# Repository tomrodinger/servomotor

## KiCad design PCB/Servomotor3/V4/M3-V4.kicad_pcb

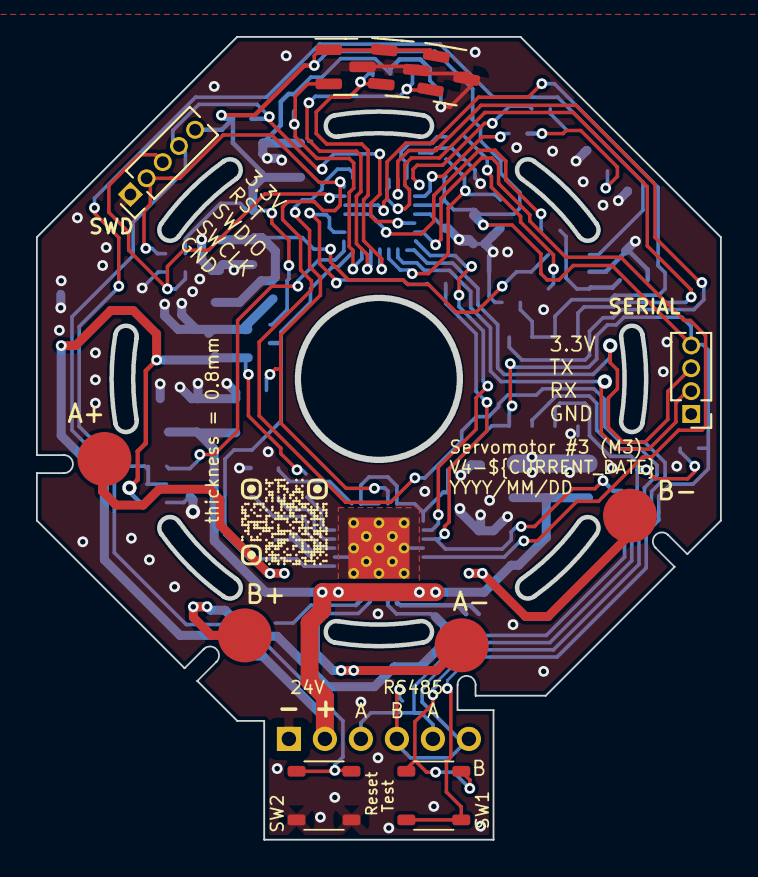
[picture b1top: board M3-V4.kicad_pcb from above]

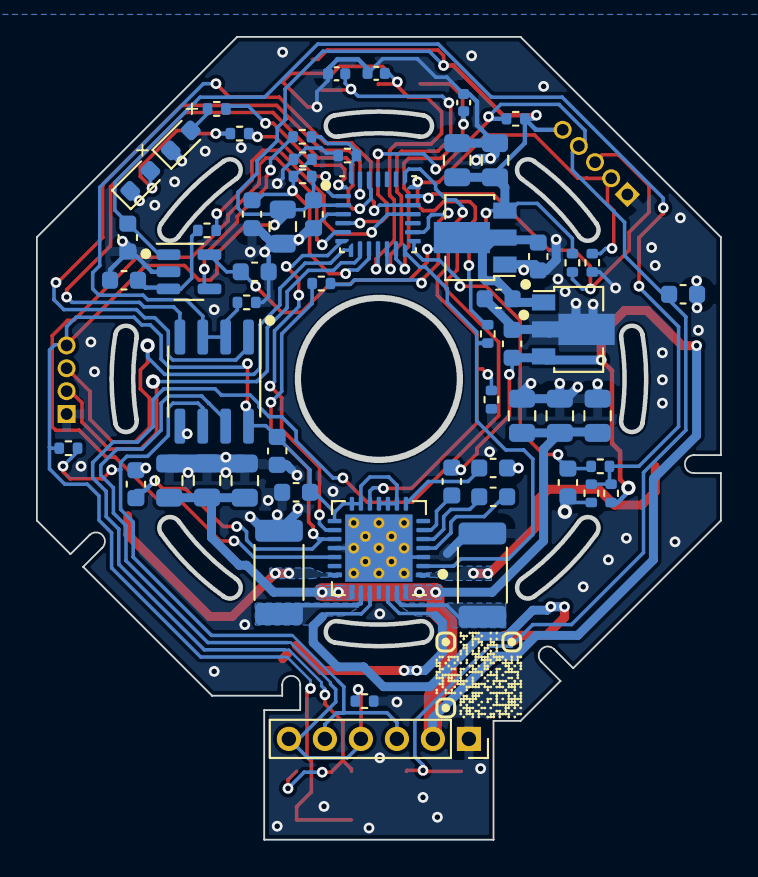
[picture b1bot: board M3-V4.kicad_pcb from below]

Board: 2 copper layers, 38.0 x 44.6 mm, 69 parts (58 on the bottom side), 44 nets.

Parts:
C1, C2, C3, C18, C25, C28, C35, C36, C37: 100nF; C_0603_1608Metric
C4, C6: 220nF; C_0603_1608Metric
C5, C7, C8, C9, C12, C14, C15, C19, C33: 4.7uF; C_0805_2012Metric
C17, C20, C23: 1nF; C_0402_1005Metric
C22, C26, C32, C41: 1uF; C_0603_1608Metric
C30: 100pF; C_0603_1608Metric
D3: KT-0603R; LED_0603_1608Metric
D4: 19-217/GHC-YR1S2/3T; LED_0603_1608Metric
J1: 01x04 male P=1.27mm; PinHeader_1x04_P1.27mm_Vertical
J2: 01x05 male P=1.27mm; PinHeader_1x05_P1.27mm_Vertical
J3, J6, J7, J8: Conn_01x01_Socket; Pad_3mm_TopOnly
J4: Conn_01x06_Socket; PinSocket_1x06_P2.00mm_Vertical
R1, R3: 270m; R_2010_5025Metric
R2, R4, R5, R7, R13, R15, R17, R20, R22, R24, R25, R27: 10k; R_0402_1005Metric
R6, R23: 5.6k; R_0402_1005Metric
R11: 470R; R_0402_1005Metric
R12: 1.5k; R_0402_1005Metric
R26: 1K; R_0402_1005Metric
R29: 4.7k; R_0402_1005Metric
SW1, SW2: TS3735PA-250gf
TH1: 100k 1% NTC; R_0402_1005Metric
U4, U6, U7: AH49HSC; SOT-23
U5: A4988; QFN-28-1EP_5x5mm_P0.5mm_EP3.75x3.75mm_ThermalVias_0.3mm
U8: STM32G031G8U6; QFN-28_4x4mm_P0.5mm
U9: LM321; SOT-23-5
U10: SP3485EN; SOIC-8_3.9x4.9mm_P1.27mm
U11: HT7533-1; SOT-89-3
U12: L78L10_SOT89; SOT-89-3

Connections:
+3.3V: C5.1, C6.1, C9.1, C33.1, C35.2, C37.1, J1.4, J2.5, R5.2, R6.2, R15.2, R17.2, R29.2, SW1.1, U4.1 (VCC), U5.9 (MS1), U5.10 (MS2), U5.11 (MS3), U5.13 (ROSC), U5.14 (~SLEEP), U5.15 (VDD), U6.1 (VCC), U7.1 (VCC), U8.3 (VDD), U10.8 (VCC), U11.3 (VOUT)
+10V: C22.1, C26.1, C32.1, U9.5 (V+), U11.2 (VIN), U12.1 (OUT)
+24V: C3.1, C7.1, C8.1, C12.1, C14.1, C15.1, C19.1, C25.1, J4.2, R27.1, U5.22 (VBB1), U5.28 (VBB2), U12.3 (IN)
/index/schTop/A: J4.3, J4.5, R17.1, U10.6 (A)
/index/schTop/B: J4.4, J4.6, R2.2, U10.7 (B)
/index/schTop/DIR: U5.19 (DIR), U8.6 (PA0)
/index/schTop/HALL1: C17.1, U7.2 (VOUT), U8.11 (PA5)
/index/schTop/HALL2: C20.1, U6.2 (VOUT), U8.12 (PA6)
/index/schTop/HALL3: C23.1, U4.2 (VOUT), U8.13 (PA7)
/index/schTop/IMCONTROL: R22.1, U8.16 (PA8)
/index/schTop/LED_GREEN: R11.1, U8.2 (PC15)
/index/schTop/LED_RED: R12.1, U8.1 (PC14)
/index/schTop/OUT1A: J7.1, U5.24 (OUT1A)
/index/schTop/OUT1B: J6.1, U5.21 (OUT1B)
/index/schTop/OUT2A: J3.1, U5.26 (OUT2A)
/index/schTop/OUT2B: J8.1, U5.1 (OUT2B)
/index/schTop/OVER_VOLTAGE: R20.2, R23.2, U8.28 (PB8)
/index/schTop/PWMOV: R25.1, U8.18 (PA11/PA9)
/index/schTop/REF24: C36.1, R24.1, U8.15 (PB1)
/index/schTop/RESET: C18.1, J2.4, R15.1, SW2.1, U8.5 (PF2)
/index/schTop/RS485_D: U8.26 (PB6), U10.4 (DI)
/index/schTop/RS485_EN: R13.2, U8.19 (PA12/PA10), U10.2 (~RE), U10.3 (DE)
/index/schTop/RS485_R: U8.27 (PB7), U10.1 (RO)
/index/schTop/STEP: U5.16 (STEP), U8.7 (PA1)
/index/schTop/SWCLK: J2.2, R4.2, SW1.2, U8.21 (PA14)
/index/schTop/SWDIO: J2.3, R5.1, U8.20 (PA13)
/index/schTop/TEMPERATURE: C41.1, R29.1, TH1.1, U8.10 (PA4)
/index/schTop/UART2 RX: J1.2, U8.9 (PA3)
/index/schTop/UART2 TX: J1.3, U8.8 (PA2)
/index/schTop/VREF: C1.1, R22.2, U5.17 (VREF)
/index/schTop/~MENABLE: R6.1, U5.2 (~ENABLE), U8.14 (PB0)
/index/schTop/~MRESET: R7.2, U5.12 (~RESET), U8.22 (PA15)
GND: C1.2, C4.1, C5.2, C6.2, C7.2, C8.2, C9.2, C12.2, C14.2, C15.2, C17.2, C18.2, C19.2, C20.2, C22.2, C23.2, C25.2, C26.2, C28.2, C30.2, C32.2, C33.2, C35.1, C36.2, C37.2, C41.2, D3.1 (K), D4.1 (K), J1.1, J2.1, J4.1, R1.1, R2.1, R3.1, R4.1, R7.1, R13.1, R23.1, R26.2, SW2.2, TH1.2, U4.3 (GND), U5.3 (GND), U5.18 (GND), U5.29 (PAD), U6.3 (GND), U7.3 (GND), U8.4 (VSS), U9.2 (V-), U10.5 (GND), U11.1 (GND), U12.2 (GND)
unnamed: D3.2 (A), R12.2
unnamed: D4.2 (A), R11.2
unnamed: R20.1, U9.4
unnamed: C2.1, U5.4 (CP1)
unnamed: C2.2, U5.5 (CP2)
unnamed: R1.2, U5.23 (SENSE1)
unnamed: R3.2, U5.27 (SENSE2)
unnamed: C3.2, U5.6 (VCP)
unnamed: C4.2, U5.8 (VREG)
unnamed: C30.1, R24.2, R26.1, R27.2, U9.1 (+)
unnamed: C28.1, R25.2, U9.3 (-)

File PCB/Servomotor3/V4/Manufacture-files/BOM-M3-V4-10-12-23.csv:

Designator,Comment,Footprint,LCSC
"C1, C2, C3, C18, C25, C28, C35, C36, C37",100nF,Capacitor_SMD:C_0603_1608Metric,C14663
"C4, C6",220nF,Capacitor_SMD:C_0603_1608Metric,C21120
"C5, C7, C8, C9, C12, C14, C15, C19, C33",4.7uF,Capacitor_SMD:C_0805_2012Metric,C1779
"C17, C20, C23",1nF,Capacitor_SMD:C_0402_1005Metric,C1523
"C22, C26, C32, C41",1uF,Capacitor_SMD:C_0603_1608Metric,C15849
C30,100pF,Capacitor_SMD:C_0603_1608Metric,C14858
D3,KT-0603R,LED_SMD:LED_0603_1608Metric,C2286
D4,19-217/GHC-YR1S2/3T,LED_SMD:LED_0603_1608Metric,C72043
"R1, R3",270m,Resistor_SMD:R_2010_5025Metric,C303758
"R2, R4, R5, R7, R13, R15, R17, R20, R22, R24, R25, R27",10k,Resistor_SMD:R_0402_1005Metric,C25744
"R6, R23",5.6k,Resistor_SMD:R_0402_1005Metric,C25908
R11,470R,Resistor_SMD:R_0402_1005Metric,C25117
R12,1.5k,Resistor_SMD:R_0402_1005Metric,C25867
R26,1K,Resistor_SMD:R_0402_1005Metric,C11702
R29,4.7k,Resistor_SMD:R_0402_1005Metric,C25900
"SW1, SW2",TS3735PA-250gf,servo_motor:TS3735PA-250gf,C393946
TH1,100k 1% NTC,Resistor_SMD:R_0402_1005Metric,C236279
"U4, U6, U7",AH49HSC,Package_TO_SOT_SMD:SOT-23,C510723
U5,A4988,servo_motor:QFN-28-1EP_5x5mm_P0.5mm_EP3.75x3.75mm_ThermalVias_0.3mm,C38437
U8,STM32G031G8U6,Package_DFN_QFN:QFN-28_4x4mm_P0.5mm,C432211
U9,LM321,Package_TO_SOT_SMD:SOT-23-5,C686636
U10,SP3485EN,Package_SO:SOIC-8_3.9x4.9mm_P1.27mm,C8963
U11,HT7533-1,Package_TO_SOT_SMD:SOT-89-3,C14289
U12,L78L10_SOT89,Package_TO_SOT_SMD:SOT-89-3,C122848

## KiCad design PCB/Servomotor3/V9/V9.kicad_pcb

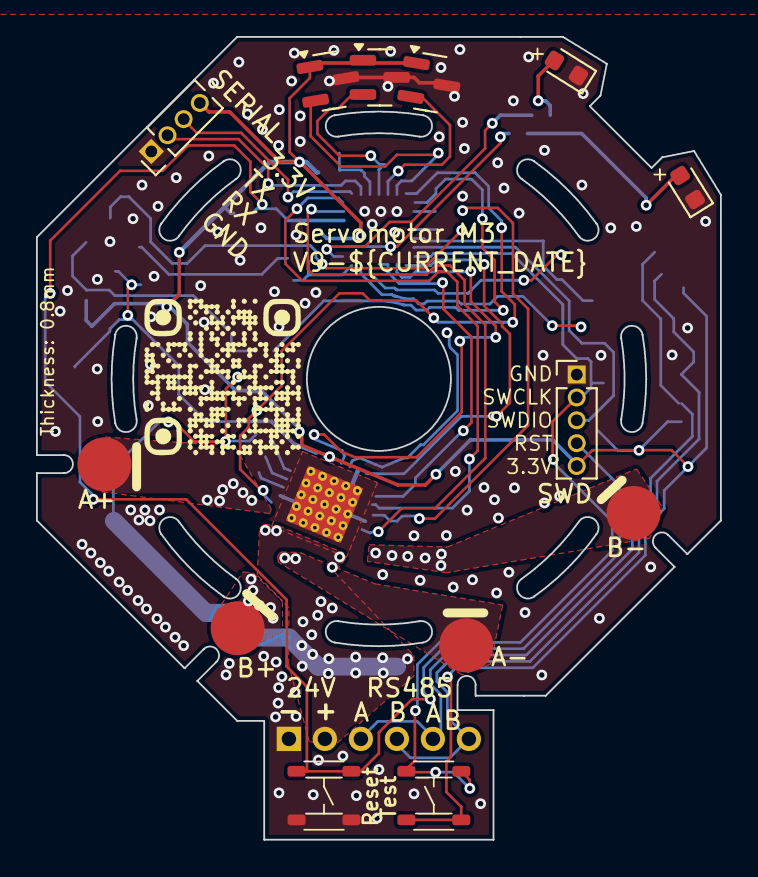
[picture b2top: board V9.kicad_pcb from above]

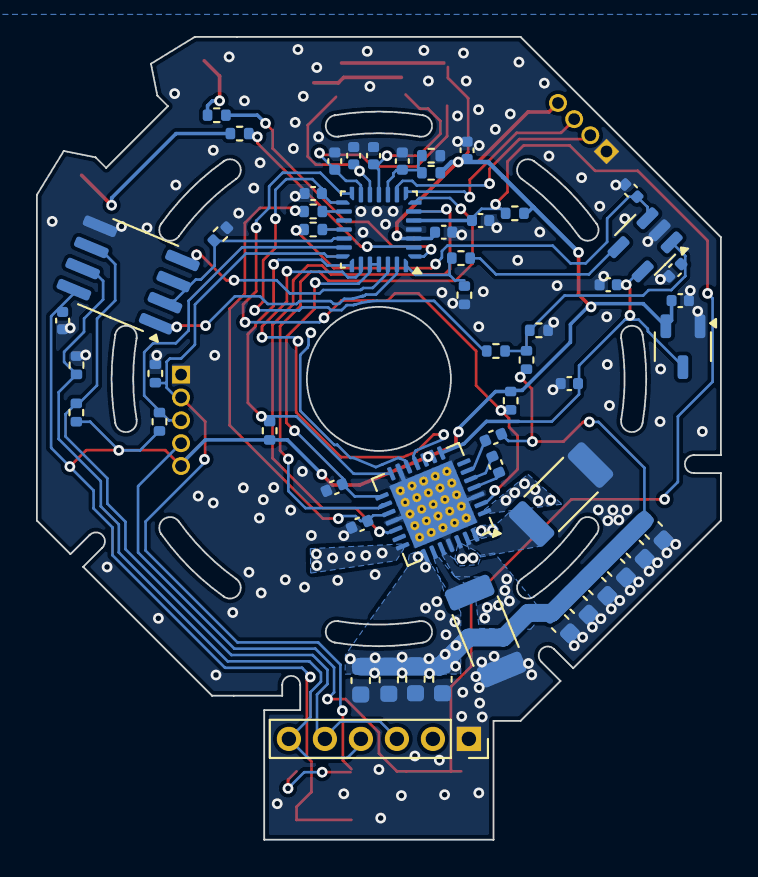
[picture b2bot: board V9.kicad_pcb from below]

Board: 2 copper layers, 38.0 x 44.6 mm, 68 parts (55 on the bottom side), 36 nets.

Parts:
C1: 10nF; C_0402_1005Metric
C2: 22nF; C_0402_1005Metric
C3, C18, C28, C35, C36, C37, C41: 100nF; C_0402_1005Metric
C4, C5: 4.7uF; C_0402_1005Metric
C6: 220nF; C_0402_1005Metric
C7, C8, C10, C11, C12, C13, C14, C15, C16, C19: 10uF; C_0603_1608Metric
C9, C22: 1uF; C_0402_1005Metric
C17, C20, C23: 1nF; C_0402_1005Metric
C30: 100pF; C_0402_1005Metric
D1: KT-0603R; LED_0603_1608Metric
D2: MHT192UGCT; LED_0603_1608Metric
J1: 01x04 male P=1.27mm; PinHeader_1x04_P1.27mm_Vertical
J2: 01x05 male P=1.27mm; PinHeader_1x05_P1.27mm_Vertical
J3, J6, J7, J8: Conn_01x01_Socket; Pad_3mm_TopOnly
J4: Conn_01x06_Socket; PinSocket_1x06_P2.00mm_Vertical
R1, R3: 150m; R_2010_5025Metric
R2, R4, R5, R6, R7, R13, R15, R17, R22, R23, R24, R25, R27: 10k; R_0402_1005Metric
R8, R12: 1.5k; R_0402_1005Metric
R11: 470R; R_0402_1005Metric
R26: 1K; R_0402_1005Metric
R29: 4.7k; R_0402_1005Metric
SW1, SW2: TS3735PA-250gf
TH1: 100k 1% NTC; R_0402_1005Metric
U1: GC6609; QFN-28-1EP_5x5mm_P0.5mm_EP3.75x3.75mm_ThermalVias
U2: STM32G031G8Ux; QFN-28_4x4mm_P0.5mm
U3: LM321; SOT-23-5
U4, U6, U7: AH49HSC; SOT-23
U10: SP3485EN; SOIC-8_3.9x4.9mm_P1.27mm
U11: XC6206PxxxMR; SOT-23-3

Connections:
+3.3V: C5.1, C9.1, C35.2, C37.1, J1.4, J2.5, R5.2, R6.2, R7.1, R15.2, R17.2, R29.2, SW1.1, U1.9 (MS1), U1.10 (MS2), U2.3 (VDD), U4.1 (VCC), U6.1 (VCC), U7.1 (VCC), U10.8 (VCC), U11.2 (VO)
+5V: C4.1, C22.1, U1.8 (VREG), U3.5 (V+), U11.3 (VI)
+24V: C3.1, C7.1, C8.1, C10.1, C11.1, C12.1, C13.1, C14.1, C15.1, C16.1, C19.1, J4.2, R27.1, U1.22 (VBB1), U1.28 (VBB1)
/index/schTop/DIR: U1.19 (DIR), U2.6 (PA0)
/index/schTop/FLAG1: U1.11 (FLAG1), U2.23 (PB3)
/index/schTop/HALL1: C17.1, U2.11 (PA5), U7.2 (VOUT)
/index/schTop/HALL2: C20.1, U2.12 (PA6), U6.2 (VOUT)
/index/schTop/HALL3: C23.1, U2.13 (PA7), U4.2 (VOUT)
/index/schTop/IMCONTROL: R22.1, U2.16 (PA8)
/index/schTop/LED_GREEN: R11.1, U2.2 (PC15)
/index/schTop/LED_RED: R12.1, U2.1 (PC14)
/index/schTop/OUT1A: J3.1, U1.24 (OUT1A)
/index/schTop/OUT1B: J6.1, U1.21 (OUT1B)
/index/schTop/OUT2A: J7.1, U1.26 (OUT2A)
/index/schTop/OUT2B: J8.1, U1.1 (OUT2B)
/index/schTop/OVER_VOLTAGE: R8.1, R23.2, U2.28 (PB8)
/index/schTop/PWMOV: R25.1, U2.18 (PA11/PA9)
/index/schTop/REF24: C36.1, R24.1, U2.15 (PB1)
/index/schTop/RESET: C18.1, J2.4, R15.1, SW2.1, U2.5 (PF2)
/index/schTop/RS485_A: J4.3, J4.5, R17.1, U10.6 (A)
/index/schTop/RS485_B: J4.4, J4.6, R2.2, U10.7 (B)
/index/schTop/RS485_D: U2.26 (PB6), U10.4 (DI)
/index/schTop/RS485_EN: R13.2, U2.19 (PA12/PA10), U10.2 (~RE), U10.3 (DE)
/index/schTop/RS485_R: U2.27 (PB7), U10.1 (RO)
/index/schTop/STEP: U1.16 (STEP), U2.7 (PA1)
/index/schTop/SWCLK: J2.2, R4.2, SW1.2, U2.21 (PA14)
/index/schTop/SWDIO: J2.3, R5.1, U2.20 (PA13)
/index/schTop/TEMPERATURE: C41.1, R29.1, TH1.1, U2.10 (PA4)
/index/schTop/UART2 RX: J1.2, U2.9 (PA3)
/index/schTop/UART2 TX: J1.3, U2.8 (PA2)
/index/schTop/VIO: C6.1, U1.15 (VIO), U2.24 (PB4), U2.25 (PB5)
/index/schTop/~HOLDEN: R7.2, U1.14 (~HOLDEN), U2.22 (PA15)
/index/schTop/~MENABLE: R6.1, U1.2 (~ENABLE), U2.14 (PB0)
GND: C1.2, C4.2, C5.2, C6.2, C7.2, C8.2, C9.2, C10.2, C11.2, C12.2, C13.2, C14.2, C15.2, C16.2, C17.2, C18.2, C19.2, C20.2, C22.2, C23.2, C28.2, C30.2, C35.1, C36.2, C37.2, C41.2, D1.1 (K), D2.1 (K), J1.1, J2.1, J4.1, R1.1, R2.1, R3.1, R4.1, R13.1, R23.1, R26.2, SW2.2, TH1.2, U1.3 (GND), U1.13 (CLK), U1.18 (GND), U1.25 (PGND), U1.29 (PAD), U2.4 (VSS), U3.2 (V-), U4.3 (GND), U6.3 (GND), U7.3 (GND), U10.5 (GND), U11.1 (GND)
unnamed: R8.2, U3.4
unnamed: C28.1, R25.2, U3.3 (-)

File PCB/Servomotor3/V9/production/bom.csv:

Designator,Footprint,Quantity,Value,LCSC Part #
C1,0402,1,10nF,C15195
"C10, C11, C12, C13, C14, C15, C16, C19, C7, C8",0603,10,10uF,C194427
"C17, C20, C23",0402,3,1nF,C1523
"C18, C28, C3, C35, C36, C37, C41",0402,7,100nF,C307331
C2,0402,1,22nF,C1532
"C22, C9",0402,2,1uF,C52923
C30,0402,1,100pF,C1546
"C4, C5",0402,2,4.7uF,C23733
C6,0402,1,220nF,C16772
D1,0603,1,KT-0603R,C2286
D2,0603,1,MHT192UGCT,C389519
J4,PinSocket_1x06_P2.00mm_Vertical,1,Conn_01x06_Socket,
"R1, R3",2010,2,150m,C421741
R11,0402,1,470R,C25117
"R12, R8",0402,2,1.5k,C25867
"R13, R15, R17, R2, R22, R23, R24, R25, R27, R4, R5, R6, R7",0402,13,10k,C25744
R26,0402,1,1K,C11702
R29,0402,1,4.7k,C25900
"SW1, SW2",TS3735PA-250gf,2,TS3735PA-250gf,C393946
TH1,0402,1,100k 1% NTC,C236279
U1,QFN-28-1EP_5x5mm_P0.5mm_EP3.75x3.75mm_ThermalVias,1,GC6609,C16197208
U10,SOIC-8_3.9x4.9mm_P1.27mm,1,SP3485EN,C8963
U11,SOT-23-3,1,XC6206PxxxMR,C5446
U2,QFN-28_4x4mm_P0.5mm,1,STM32G031G8Ux,C432211
U3,SOT-23-5,1,LM321,C19723728
"U4, U6, U7",SOT-23,3,AH49HSC,C510723
